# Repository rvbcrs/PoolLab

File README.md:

## Pura — ESP32‑S3 zwembadmonitor (pH, ORP, Temp · LVGL · MQTT · Zigbee)

### Wat het doet
- **pH en ORP meten** via analoge PH‑4502C/ORP‑4502C sensorbordjes (MCP6002 op 3.3 V) rechtstreeks op de ESP32 ADC.
- **Twee modi**: schakel tussen **Zigbee** en **WiFi/MQTT** via een UI‑toggle. De keuze wordt persistent opgeslagen (NVS) en bij boot toegepast.
- **MQTT integratie**: publiceert pH/ORP/temperatuur en biedt Home Assistant auto‑discovery + command topics om drempels te wijzigen.
- **Doseer‑pompen**: twee peristaltische pompen (pH/ORP) via TB6612FNG driver, met PWM‑snelheidsregeling vanuit de LVGL‑UI.
- **Safety**: limieten voor dagvolume, sessieduur en pH/ORP sanity; automatische noodstop + WhatsApp‑notificatie.
- **Zigbee commissioning**: lange druk op BOOT (>3 s) start commissioning; WiFi wordt tijdelijk uitgezet.

---

### Primaire hardware

| Onderdeel | Omschrijving |
|-----------|-------------|
| **MCU** | JC3248W535 — ESP32‑S3, 3.5" IPS 320×480 QSPI display, capacitief touch |
| **Sensoren** | 2× PH‑4502C bordje (één voor pH, één voor ORP), LM358 vervangen door **MCP6002** |
| **Motor driver** | SparkFun ROB‑14450 / TB6612FNG |
| **Pompen** | 2× peristaltische pomp (pH‑dosering en ORP/chloor‑dosering) |

---

### Sensor bekabeling (PH‑4502C met MCP6002 op 3.3 V)

> **Belangrijk:** Voed het bordje op **3.3 V**, niet 5 V.
> De MCP6002 is rail‑to‑rail (1.8–6 V). Bij 5 V kan de analoge output bij zuur water boven 3.3 V uitkomen en de ESP32 ADC beschadigen.

```
PH‑4502C (pH bordje)        JC3248W535 (ESP32‑S3)
  VCC  ──────────────────────  3.3 V
  GND  ──────────────────────  GND
  PO   ──────────────────────  GPIO6   (ADC1_CH5)
  DO   niet aansluiten
  TO   niet aansluiten
  BNC  ←── pH‑electrode

PH‑4502C (ORP bordje)       JC3248W535 (ESP32‑S3)
  VCC  ──────────────────────  3.3 V
  GND  ──────────────────────  GND
  PO   ──────────────────────  GPIO7   (ADC1_CH6)
  DO   niet aansluiten
  TO   niet aansluiten
  BNC  ←── ORP‑electrode
```

GPIO6 en GPIO7 zijn vrije ADC1‑pinnen (geen WiFi‑conflict). De overige ADC1‑pinnen zijn in gebruik door QSPI‑display (21/39/40/45/47/48), touch I2C (4/8), motoren (9/14–18) en I2S‑speaker (2/41/42).

**Testen zonder probe:**
Verbind de BNC center pin met de BNC outer ring via een 10 kΩ weerstand → simuleert 0 mV (pH 7 / 0 mV ORP) → de display toont ~pH 7.0 en ~0 mV.

**Platformio.ini flags (al ingesteld voor `esp32‑s3‑35`):**
```ini
-D USE_ANALOG_SENSORS=1
-D PH_ADC_PIN=6
-D ORP_ADC_PIN=7
```

**Kalibratie defaults (MCP6002 op 3.3 V, gain ≈ 5.2×):**
| Punt | Spanning |
|------|---------|
| pH 4 | ≈ 2.58 V |
| pH 7 | ≈ 1.65 V (mid‑supply) |
| pH 10 | ≈ 0.72 V |
| ORP 0 mV | ≈ 1.65 V |

Kalibreer altijd met pH 4 en pH 7 buffervloeistof voor nauwkeurige metingen. Waarden worden opgeslagen in NVS via WebUI → Settings → Calibration.

---

### Wiring diagrams

**ESP32‑S3 — Analoge sensoren (PH‑4502C met MCP6002)**

```mermaid
flowchart LR
  PH_PROBE["pH‑electrode\n(BNC)"] --> PH_BOARD["PH‑4502C\n(MCP6002 op 3.3 V)"]
  ORP_PROBE["ORP‑electrode\n(BNC)"] --> ORP_BOARD["PH‑4502C ORP\n(MCP6002 op 3.3 V)"]
  PH_BOARD  --"PO → GPIO6"--> MCU["JC3248W535\nESP32‑S3"]
  ORP_BOARD --"PO → GPIO7"--> MCU
  V33["3.3 V"] --> PH_BOARD
  V33         --> ORP_BOARD
  GND["GND"]  --> PH_BOARD
  GND         --> ORP_BOARD
  GND         --> MCU
```

**ESP32‑C6 — ADS1115 via I2C**

```mermaid
flowchart LR
  PH_PROBE["pH‑electrode\n(BNC)"] --> PH_BOARD["PH‑4502C"]
  ORP_PROBE["ORP‑electrode\n(BNC)"] --> ORP_BOARD["PH‑4502C ORP"]
  PH_BOARD  --"AO → A0"--> ADS["ADS1115\n(0x48)"]
  ORP_BOARD --"AO → A1"--> ADS
  ADS --"SDA → GPIO18"--> MCU["ESP32‑C6"]
  ADS --"SCL → GPIO19"--> MCU
  V33["3.3 V"] --> ADS
  GND["GND"]   --> ADS
  GND          --> MCU
```

**ESP32‑S3 — Motor driver (TB6612FNG)**

```mermaid
flowchart LR
  MCU["JC3248W535\nESP32‑S3"] --"GPIO15 IN1\nGPIO16 IN2\nGPIO17 PWM"--> M1["TB6612\nMotor A"]
  MCU --"GPIO18 IN1\nGPIO14 IN2\nGPIO9 PWM"--> M2["TB6612\nMotor B"]
  MCU --"GPIO46 STBY"--> M1
  MCU --"GPIO46 STBY"--> M2
  M1 --"A01/A02"--> PUMP1["pH‑pomp"]
  M2 --"B01/B02"--> PUMP2["ORP‑pomp"]
  VM["6–12 V"] --> M1
  VM           --> M2
```

---

### ADS1115 (ESP32‑C6 build)

De C6‑build (`esp32‑c6‑147`) leest pH en ORP via een ADS1115 16‑bit ADC op I2C:

```
ADS1115          ESP32‑C6
  VDD ────────── 3.3 V
  GND ────────── GND
  SDA ────────── GPIO18
  SCL ────────── GPIO19
  A0  ────────── pH AO
  A1  ────────── ORP AO
```

Flags (al ingesteld):
```ini
-D USE_ADS1115=1
-D ADS_ADDR=0x48
-D ADS_SDA=18
-D ADS_SCL=19
-D ADS_CH_PH=0
-D ADS_CH_ORP=1
```

---

### Motor driver bekabeling (TB6612FNG — ESP32‑S3)

```
TB6612FNG        JC3248W535 (ESP32‑S3)
  VCC  ────────── 3.3 V  (logica)
  GND  ────────── GND
  VM   ────────── motorspanning (6–12 V)
  STBY ────────── GPIO46

  AIN1 ────────── GPIO15  (M1 IN1 / pH pomp)
  AIN2 ────────── GPIO16  (M1 IN2)
  PWMA ────────── GPIO17  (M1 PWM — LEDC CH5 / Timer 3)

  BIN1 ────────── GPIO18  (M2 IN1 / ORP pomp)
  BIN2 ────────── GPIO14  (M2 IN2)
  PWMB ────────── GPIO9   (M2 PWM — LEDC CH4 / Timer 2)

  A01/A02 ─────── Motor 1 (pH‑pomp)
  B01/B02 ─────── Motor 2 (ORP‑pomp)
```

- GPIO46 is een strapping pin; zorg dat STBY niet omlaag trekt tijdens boot.
- PWM: 10 kHz, 8‑bit. Snelheden instelbaar in LVGL‑UI en opgeslagen in NVS.

---

### Pump Flow Tracking & Kalibratie

**Wat wordt bijgehouden:**
- Real‑time flow rate (ml/min) tijdens pompen
- Session volume (ml) — reset bij stop
- Daily volume — reset automatisch om 00:00
- Total volume — handmatig reset via WebUI

**Flow kalibreren:**
1. WebUI → Settings → "Pump Flow Rate (ml/min @ 100%)"
2. Laat pomp 60 s @ 100% draaien, meet volume in maatbeker
3. Flow rate = gemeten volume / 1 minuut
4. Systeem schaalt automatisch voor lagere snelheden (bijv. 60% = 0.6 × gekalibreerde waarde)

---

### Safety Features & Emergency Stop

**Limieten (instelbaar in `src/main.cpp`):**
```cpp
MAX_DAILY_VOLUME     = 500.0f;  // ml/dag per pomp
MAX_SESSION_VOLUME   = 200.0f;  // ml per aanslag
MAX_SESSION_DURATION = 120;     // seconden per aanslag
PH_SANITY_MIN        = 4.0f;
PH_SANITY_MAX        = 10.0f;
ORP_SANITY_MIN       = -500.0f;
ORP_SANITY_MAX       = 1500.0f;
SENSOR_TIMEOUT       = 300;     // seconden zonder data → alarm
```

**Gedrag bij trigger:**
- Alle pompen direct gestopt
- Rode banner op LVGL UI: `⚠️ EMERGENCY STOP - <reden>`
- MQTT alert op `pool/alert/<type>`
- WhatsApp‑bericht via CallMeBot

**WhatsApp Setup (CallMeBot):**
1. Verkrijg API key via https://www.callmebot.com/blog/free-api-whatsapp-messages/
2. WebUI → Safety → telefoonnummer (bijv. `31612345678`) + API key invullen
3. Test via "Send Test Alert" button

**MQTT Alert Topics:**
```
pool/alert/daily_limit_m1      pool/alert/daily_limit_m2
pool/alert/session_volume_m1   pool/alert/session_volume_m2
pool/alert/session_duration_m1 pool/alert/session_duration_m2
pool/alert/ph_sanity_low       pool/alert/ph_sanity_high
pool/alert/orp_sanity_low      pool/alert/orp_sanity_high
pool/alert/ph_sensor_timeout   pool/alert/orp_sensor_timeout
```

---

### Bouwen en flashen

Primaire build (ESP32‑S3 35"):
```bash
pio run -e esp32-s3-35 -t upload --upload-port <ip>   # OTA
pio run -e esp32-s3-35 -t upload                       # USB
```

C6 build:
```bash
pio run -e esp32-c6-147 -t upload
```

Seriële monitor: 115200 baud.

---

### Configuratie

**WiFi** via captive portal:
- Bij lege WiFi‑gegevens start automatisch AP `Pura‑Setup`.
- Verbind → open willekeurige URL → vul SSID/wachtwoord in → Save & Reboot.
- Of via Settings → Network → Configure WiFi.

**MQTT** instelbaar via WebUI → Settings (host/port/user/pass) of in `src/main.cpp`:
```cpp
MQTT_HOST, MQTT_PORT, MQTT_USER, MQTT_PASS, MQTT_CLIENTID
```

**OTA:** hostnaam `pura-XXXXXX` (chip‑ID). Upload via PlatformIO "Upload using network" of ArduinoOTA.

---

### MQTT Topics

State:
```
pool/sensor/ph
pool/sensor/orp
pool/sensor/temp
```

Home Assistant discovery:
```
homeassistant/sensor/pool_ph/config
homeassistant/sensor/pool_orp/config
homeassistant/sensor/pool_temp/config
```

Drempels (write/echo):
```
pool/cmd/ph_min  ↔  pool/cfg/ph_min
pool/cmd/ph_max  ↔  pool/cfg/ph_max
pool/cmd/orp_min ↔  pool/cfg/orp_min
pool/cmd/orp_max ↔  pool/cfg/orp_max
```

---

### WebUI

| URL | Pagina |
|-----|--------|
| `http://<ip>/` | Live sensor tiles + pump stats (WebSocket) |
| `http://<ip>/settings` | pH/ORP drempels, pompsnelheden, flow kalibratie, MQTT |
| `http://<ip>/safety` | Emergency status, WhatsApp config, volume resets, test alerts |

WebSocket op poort 81.

---

### LVGL UI

- **ESP32‑S3 (3.5"):** 3‑card UI (pH / ORP / Temp), moderne donkere tegels, pump stats boven motoricoon, emergency banner.
- **ESP32‑C6 (1.47"):** Compacte tileview (pH/ORP).
- Watchdog S3: heartbeat uit BSP‑task; herbouwt UI als >8 s stil → `S3 LVGL watchdog: rebuild complete`.
- Touch: debouncing ingebouwd, geen key‑repeat.

---

### Projectstructuur

| Bestand | Rol |
|---------|-----|
| `src/main.cpp` | Bootvolgorde, WiFi/MQTT, Zigbee, periodic publish, safety |
| `src/core/Storage.{h,cpp}` | NVS wrapper (drempels, snelheden, modus, volumes, config) |
| `src/core/boards/Esp32S3Board.{h,cpp}` | S3 board: display, touch, pins, LVGL lock |
| `src/core/boards/Esp32C6Board.{h,cpp}` | C6 board |
| `src/boards/BoardSelect.{h,cpp}` | Board‑selectie op basis van build flag |
| `src/domain/Metrics.{h,cpp}` | Laatste pH/ORP/temp; bron voor UI en MQTT |
| `src/domain/ControlPolicy.{h,cpp}` | Safety logic, sanity checks, emergency stop |
| `src/io/AnalogPhOrpSensor.h` | ADC‑lezer voor PH‑4502C via ESP32 ADC (S3) |
| `src/io/AdsPhOrpSensor.{h,cpp}` | ADS1115 I2C lezer voor pH/ORP (C6) |
| `src/io/MotorController.h` | Motor state machine, LEDC PWM, flow tracking |
| `src/io/MqttClient.{h,cpp}` | PubSubClient: discovery, publish, command topics, alerts |
| `src/io/WebUI.{h,cpp}` | Async web server: homepage, settings, safety, WebSocket, API |
| `src/io/ZigbeeClient.{h,cpp}` | Zigbee abstractie (C6; no‑op op S3) |
| `src/ui/UI.{h,cpp}` | LVGL UI builder (3‑card S3 / tileview C6), emergency banner |
| `src/domain/DummySensor.h` | Gesimuleerde sensordata voor testen |
| `src/fonts`, `src/images` | LVGL assets (fonts, iconen) |

---

### Troubleshooting

**pH/ORP waarden kloppen niet:**
- Kalibreer met pH 4 en pH 7 buffervloeistof via WebUI → Settings → Calibration.
- Check de spanning op PO met een multimeter: bij VCC=3.3 V moet pH 7 ≈ 1.65 V geven.
- Zorg dat VCC van het sensorbordje echt 3.3 V is (niet 5 V).

**WiFi "NO_AP_FOUND":** controleer SSID/ontvangst; auto‑reconnect + periodieke hard restart.

**MQTT extern werkt niet, lokaal wel:**
- Cloudflare DNS: zet op "DNS only" (grijze wolk) voor raw TCP.
- NPM: gebruik Streams (TCP), geen Proxy Host.
- Test met `mosquitto_sub/pub` voordat je het device test.

**Pompen werken niet:**
- Console: `[MOTOR] Check: MOTOR_ENABLE=1 motorsEnabled=?` — beide moeten 1 zijn.
- WebUI → Settings → vink "Enable pH/ORP dosing pumps" aan → Save.

**Emergency stop reset niet automatisch:**
- Sanity alerts: wacht tot sensorwaarden terug binnen limieten zijn.
- Volume/duration limits: reset device of wacht tot 00:00 (daily reset).

**WhatsApp notificaties werken niet:**
- Telefoonnummer met landcode (bijv. `31612345678`).
- Test via CallMeBot website om te bevestigen dat account actief is.
- Console: zoek naar `[SAFETY] WhatsApp API response: 200`.

---

### Changelog

**Huidig:**
- ✅ Tuya UART sniffer verwijderd — alle sensordata nu via directe hardware (ADC / ADS1115).
- ✅ PH‑4502C analoge sensoren op GPIO6 (pH) en GPIO7 (ORP) — MCP6002 op 3.3 V.
- ✅ Kalibratie defaults aangepast voor MCP6002 op 3.3 V (mid‑supply = 1.65 V).
- ✅ Zigbee `onPh/OrpMinMaxWrite` stubs voor non‑Zigbee builds (fix compile‑fout S3).
- ✅ `core::Board.h` include toegevoegd aan `UI.cpp` (fix `UiConfig` compile‑fout).
- ✅ Backup‑bestanden opgeruimd (`AnalogPhOrpSensor 2.h`, `AdsPhOrpSensor 2.*`).

**Eerder:**
- ✅ Pump flow tracking: ml/min, session, daily (auto‑reset 00:00), total.
- ✅ Safety limits: daily/session volume, session duration, pH/ORP sanity, sensor timeout.
- ✅ Emergency stop: noodstop + rode LVGL banner.
- ✅ WhatsApp notificaties via CallMeBot (async task).
- ✅ MQTT alert topics `pool/alert/<type>`.
- ✅ WebUI Safety page, Settings gereorganiseerd met emoji‑headers.
- ✅ Unieke MQTT clientId per device (chip‑ID).
- ✅ Exponential backoff bij MQTT reconnect.
- ✅ LVGL watchdog voor C6 en S3.
- ✅ Touch debouncing (geen key‑repeat).
- ✅ Reset WiFi knop via captive portal.

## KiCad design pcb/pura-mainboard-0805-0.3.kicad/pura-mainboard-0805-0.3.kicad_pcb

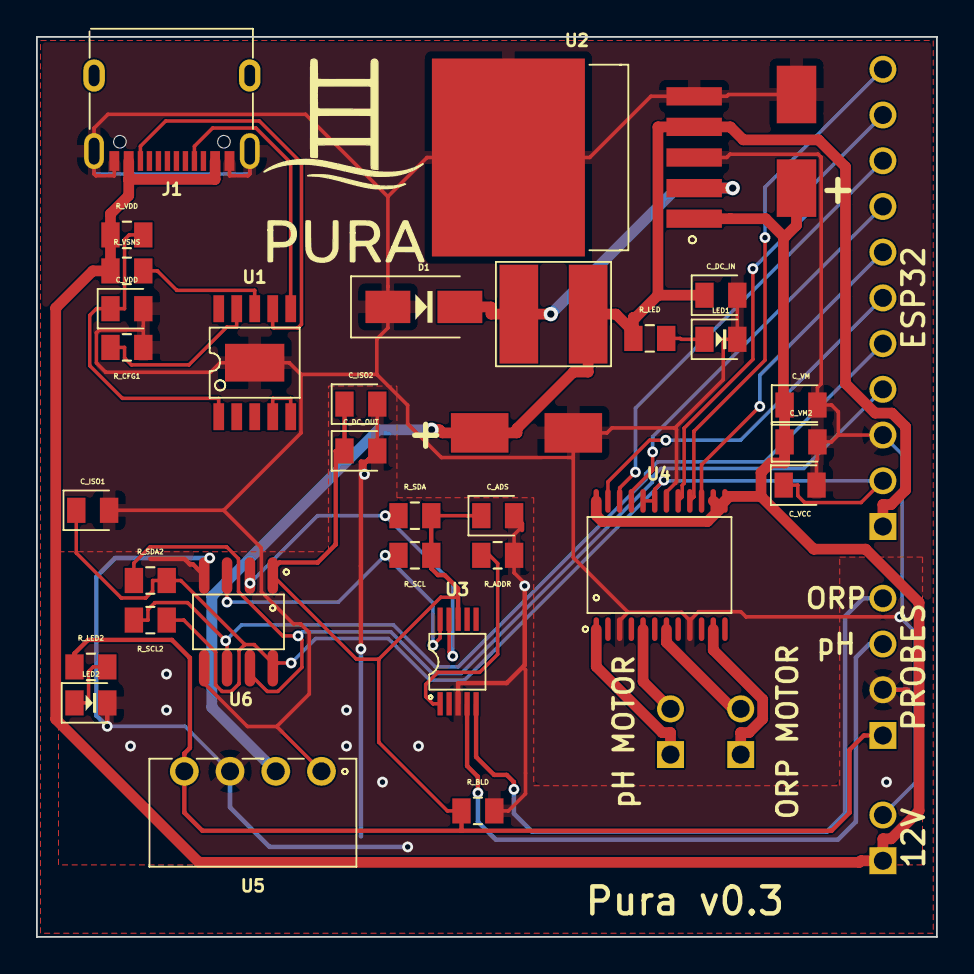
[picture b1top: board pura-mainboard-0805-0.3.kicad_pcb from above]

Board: 2 copper layers, 50.0 x 50.0 mm, 38 parts (0 on the bottom side), 32 nets.

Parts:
C_ADS: 100nF; capacitor_0805
C_DC_IN: 10uF; capacitor_0805
C_DC_OUT: 10uF; capacitor_0805
C_IN: 100uF; capacitor
C_ISO1, C_ISO2: 100nF; capacitor_0805
C_OUT: 220uF; capacitor
C_VCC: 100nF; capacitor_0805
C_VDD: 1uF; capacitor_0805
C_VM: 10uF; capacitor_0805
C_VM2: 100nF; capacitor_0805
D1: D; SS34
J1: TYPE_C_16PIN_2MD_073_; TYPE_C_16PIN_2MD_073
J_12V: J_12V; pin_header_pinrow2_nopinlabels
J_ESP: J_ESP; pin_header_pinrow11_nopinlabels
J_M1: J_M1; pin_header_pinrow2_nopinlabels
J_M2: J_M2; pin_header_pinrow2_nopinlabels
J_PROBE: J_PROBE; pin_header_pinrow4_nopinlabels
L1: 33H; inductor
LED1: LED; led_0805_color(green)
LED2: LED; led_0805_color(cyan)
R_ADDR: 0Ω; resistor_res0805
R_BLD: 330Ω; resistor_res0805
R_CFG1: 24kΩ; resistor_res0805
R_LED, R_LED2: 2.2kΩ; resistor_res0805
R_SCL, R_SCL2: 4.7kΩ; resistor_res0805
R_SDA, R_SDA2: 4.7kΩ; resistor_res0805
R_VDD: 1kΩ; resistor_res0805
R_VSNS: 10kΩ; resistor_res0805
U1: CH224K
U2: LM2596S_5_0_UMW_; LM2596S_5_0_UMW
U3: ADS1115IDGST
U4: TB6612FNG_C_8_EL
U5: B0505S_1WR3
U6: ADUM1250ARZ_RL7

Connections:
.J1 > .A4B9 to .R_VDD > .pin1: C_IN.1, C_VM.1, C_VM2.1, J1.18, J1.27, J_12V.1, R_VDD.1, R_VSNS.1, U2.1, U4.13, U4.14, U4.24
.J1 > .A5 to .U1 > .CC2: J1.20, U1.6
.J1 > .B5 to .U1 > .CC1: J1.26, U1.7
.J_ESP > .SCL to .U6 > .SCL2: J_ESP.5, R_SCL2.1, U6.6
.J_ESP > .SDA to .U6 > .SDA2: J_ESP.4, R_SDA2.1, U6.7
.J_ESP > .V33 to .U4 > .VCC: C_ISO1.1, C_VCC.1, J_ESP.2, R_SCL2.2, R_SDA2.2, U4.19, U4.20, U6.8
.L1 > .pin2 to .U2 > .FB: C_DC_IN.1, C_OUT.1, J_ESP.1, L1.2, R_LED.1, U2.4, U5.2
.R_LED2 > .pin2 to .LED2 > .pin1: LED2.1, R_LED2.2
.R_LED > .pin2 to .LED1 > .pin1: LED1.1, R_LED.2
.R_VDD > .pin2 to .U1 > .VDD: C_VDD.1, R_VDD.2, U1.1
.R_VSNS > .pin2 to .U1 > .VBUS: R_VSNS.2, U1.8
.U1 > .CFG1 to .R_CFG1 > .pin1: R_CFG1.1, U1.9
.U1 > .DP to .U1 > .DM: U1.4, U1.5
.U2 > .OUT to .L1 > .pin1: D1.2, L1.1, U2.2
.U3 > .ADDR to .R_ADDR > .pin1: R_ADDR.1, U3.1
.U3 > .AIN0 to .J_PROBE > .PH_PO: J_PROBE.3, U3.4
.U3 > .AIN1 to .J_PROBE > .ORP_PO: J_PROBE.4, U3.5
.U3 > .SCL to .R_SCL > .pin1: R_SCL.1, U3.10, U6.3
.U3 > .SDA to .R_SDA > .pin1: R_SDA.1, U3.9, U6.2
.U4 > .AIN1 to .J_ESP > .AIN1: J_ESP.8, U4.21
.U4 > .AIN2 to .J_ESP > .AIN2: J_ESP.9, U4.22
.U4 > .AO11 to .J_M1 > .MA1: J_M1.1, U4.1
.U4 > .AO21 to .J_M1 > .MA2: J_M1.2, U4.5
.U4 > .BIN1 to .J_ESP > .BIN1: J_ESP.10, U4.17
.U4 > .BIN2 to .J_ESP > .BIN2: J_ESP.11, U4.16
.U4 > .BO11 to .J_M2 > .MB1: J_M2.1, U4.11
.U4 > .BO21 to .J_M2 > .MB2: J_M2.2, U4.7
.U4 > .PWMA to .J_ESP > .PWMA: J_ESP.6, U4.23
.U4 > .PWMB to .J_ESP > .PWMB: J_ESP.7, U4.15
.U5 > .pin4 to .U6 > .VDD1: C_ADS.1, C_DC_OUT.1, C_ISO2.1, J_PROBE.1, R_BLD.1, R_LED2.1, R_SCL.2, R_SDA.2, U3.8, U5.4, U6.1
AGND: C_ADS.2, C_DC_OUT.2, C_ISO2.2, J_PROBE.2, LED2.2, R_ADDR.2, R_BLD.2, U3.3, U5.3, U6.4
GND: C_DC_IN.2, C_IN.2, C_ISO1.2, C_OUT.2, C_VCC.2, C_VDD.2, C_VM.2, C_VM2.2, D1.1, J1.13, J1.14, J1.17, J1.28, J_12V.2, J_ESP.3, LED1.2, R_CFG1.2, U1.11, U2.3, U2.5, U2.6, U4.3, U4.9, U4.18, U5.1, U6.5

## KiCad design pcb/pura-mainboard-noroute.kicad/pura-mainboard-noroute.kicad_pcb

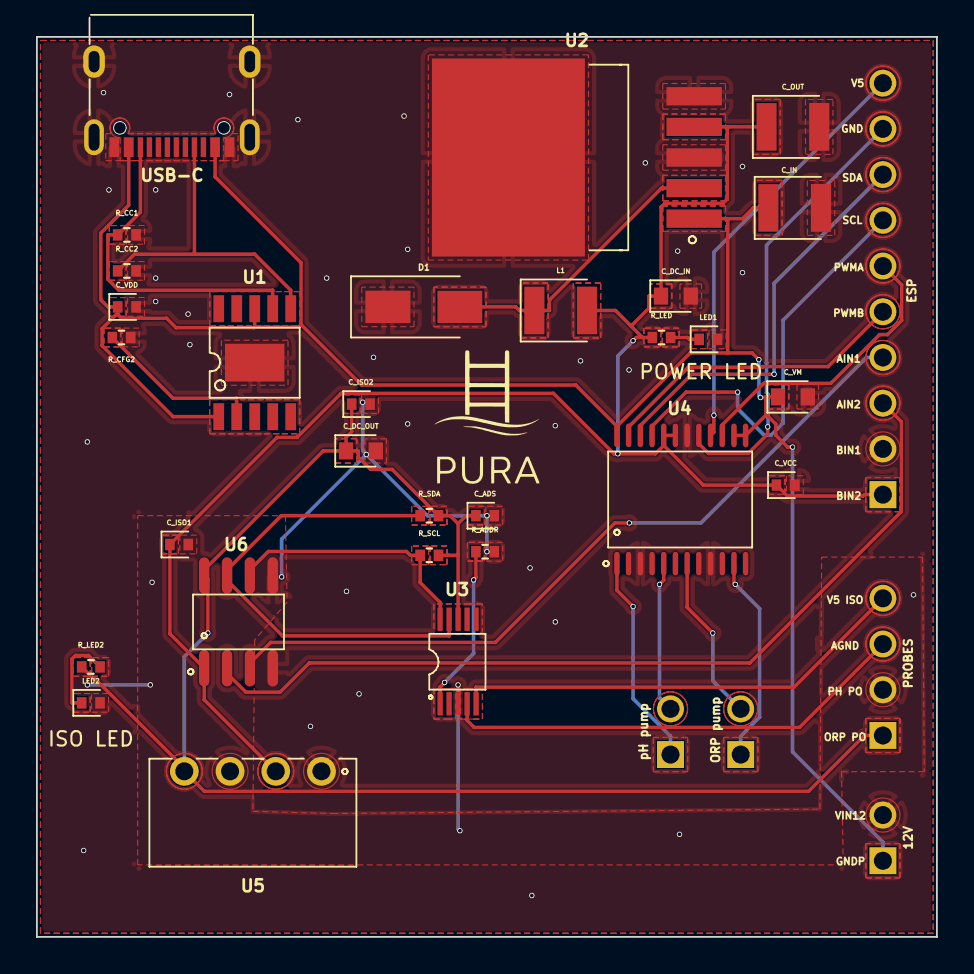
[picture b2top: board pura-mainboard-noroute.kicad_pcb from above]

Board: 2 copper layers, 50.0 x 50.0 mm, 34 parts (0 on the bottom side), 28 nets.

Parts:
12V: J_12V; pin_header_pinrow2_nopinlabels
C_ADS: 100nF; capacitor_0402
C_DC_IN: 10uF; capacitor_0603
C_DC_OUT: 10uF; capacitor_0603
C_IN: 220uF; capacitor_1210
C_ISO1, C_ISO2: 100nF; capacitor_0402
C_OUT: 220uF; capacitor_1210
C_VCC: 100nF; capacitor_0402
C_VDD: 100nF; capacitor_0402
C_VM: 10uF; capacitor_0603
D1: D; SS34
ESP: J_ESP; pin_header_pinrow10_nopinlabels
L1: 33H; inductor_1210
LED1: LED; led_0402_color(green)
LED2: LED; led_0402_color(cyan)
MOTOR 1: J_M1; pin_header_pinrow2_nopinlabels
ORP pump: J_M2; pin_header_pinrow2_nopinlabels
PROBES: J_PROBE; pin_header_pinrow4_nopinlabels
R_ADDR: 0Ω; resistor_res0402
R_CC1, R_CC2: 5.1kΩ; resistor_res0402
R_CFG2: 0Ω; resistor_res0402
R_LED, R_LED2: 2.2kΩ; resistor_res0402
R_SCL: 4.7kΩ; resistor_res0402
R_SDA: 4.7kΩ; resistor_res0402
U1: CH224K
U2: LM2596S_5_0_UMW_; LM2596S_5_0_UMW
U3: ADS1115IDGST
U4: TB6612FNG_C_8_EL
U5: B0505S_1WR3
U6: ADUM1250ARZ_RL7
USB-C: TYPE_C_16PIN_2MD_073_; TYPE_C_16PIN_2MD_073

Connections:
.J1 > .A5 to .U1 > .CC2: R_CC2.1, U1.6, USB-C.20
.J1 > .B5 to .U1 > .CC1: R_CC1.1, U1.7, USB-C.26
.J_ESP > .SCL to .U6 > .SCL1: ESP.4, U6.3
.J_ESP > .SDA to .U6 > .SDA1: ESP.3, U6.2
.L1 > .pin2 to .U2 > .FB: C_DC_IN.1, C_ISO1.1, C_OUT.1, C_VCC.1, ESP.1, L1.2, R_LED.1, U2.4, U4.19, U4.20, U5.2, U6.1
.R_LED2 > .pin2 to .LED2 > .pin1: LED2.1, R_LED2.2
.R_LED > .pin2 to .LED1 > .pin1: LED1.1, R_LED.2
.U1 > .CFG2 to .R_CFG2 > .pin1: R_CFG2.1, U1.2
.U1 > .VDD to .U1 > .VBUS: 12V.1, C_IN.1, C_VDD.1, C_VM.1, U1.1, U1.8, U2.1, U4.13, U4.14, U4.24, USB-C.18, USB-C.27
.U2 > .OUT to .L1 > .pin1: D1.2, L1.1, U2.2
.U3 > .ADDR to .R_ADDR > .pin1: R_ADDR.1, U3.1
.U3 > .AIN0 to .J_PROBE > .PH_PO: PROBES.3, U3.4
.U3 > .AIN1 to .J_PROBE > .ORP_PO: PROBES.4, U3.5
.U3 > .SCL to .R_SCL > .pin1: R_SCL.1, U3.10, U6.6
.U3 > .SDA to .R_SDA > .pin1: R_SDA.1, U3.9, U6.7
.U4 > .AIN1 to .J_ESP > .AIN1: ESP.7, U4.21
.U4 > .AIN2 to .J_ESP > .AIN2: ESP.8, U4.22
.U4 > .AO11 to .J_M1 > .MA1: MOTOR 1.1, U4.1
.U4 > .AO21 to .J_M1 > .MA2: MOTOR 1.2, U4.5
.U4 > .BIN1 to .J_ESP > .BIN1: ESP.9, U4.17
.U4 > .BIN2 to .J_ESP > .BIN2: ESP.10, U4.16
.U4 > .BO11 to .J_M2 > .MB1: ORP pump.1, U4.11
.U4 > .BO21 to .J_M2 > .MB2: ORP pump.2, U4.7
.U4 > .PWMA to .J_ESP > .PWMA: ESP.5, U4.23
.U4 > .PWMB to .J_ESP > .PWMB: ESP.6, U4.15
.U5 > .pin4 to .U6 > .VDD2: C_ADS.1, C_DC_OUT.1, C_ISO2.1, PROBES.1, R_LED2.1, R_SCL.2, R_SDA.2, U3.8, U5.4, U6.8
AGND: C_ADS.2, C_DC_OUT.2, C_ISO2.2, LED2.2, PROBES.2, R_ADDR.2, U3.3, U5.3, U6.5
GND: 12V.2, C_DC_IN.2, C_IN.2, C_ISO1.2, C_OUT.2, C_VCC.2, C_VDD.2, C_VM.2, D1.1, ESP.2, LED1.2, R_CC1.2, R_CC2.2, R_CFG2.2, U1.11, U2.3, U2.5, U2.6, U4.3, U4.9, U4.18, U5.1, U6.4, USB-C.13, USB-C.14, USB-C.15, USB-C.16, USB-C.17, USB-C.28

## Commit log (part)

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2025-09-10 Working version
2025-09-11 Refactor into logical structure
2025-09-12 First Zigbee implementation
2025-09-13 WIP zigbee sensors
2025-09-13 Working zigbee tx
2025-09-13 Touch fix
2025-09-13 Icons for zigbee connection
2025-09-13 Zigbee iJoined()
2025-09-13 Settings screen cleanup and zigbee bugfix
2025-09-14 Readme update and zigbee / wifi toggle fix
2025-09-15 Wifi Captha portal and OTA
2025-09-15 Unique ChipID for OTA and capcha
2025-09-15 Simple WebUI and readme update
2025-09-17 ESP32-S3-JC3248W535 board added
2025-09-19 Multiboard support and refactoring code from main
2025-09-22 UI fixes and further main cleanup
2025-09-22 More refactoring of main
2025-09-22 refactor main
2025-09-23 Settings bug fixes
2025-09-23 MQTT issues fix
2025-09-23 Removed debug logging mqtt
2025-09-24 MQTT fixes
2025-09-24 C6 Legacy ui deleted
2025-09-25 Temperature colored tile
2025-09-25 ADS1115 and ESP32 ADC sensor readings
2025-09-25 Readme mermaid fix
2025-10-02 Added flow and fixed touch
2025-10-04 Added fuel security and safety features
2025-10-06 Initial P4 board added
2025-10-09 Pump flow fix in ui
2025-10-09 Zigbee mode enabled for P4
2025-10-14 Fixes for P4
2025-10-21 Add ESP32-P4 display libraries (st7701_lcd + gt911_touch)
    - Added st7701_lcd library for MIPI-DSI LCD driver
    - Added gt911_touch library for capacitive touch driver
    - Libraries moved from lib_p4 to libraries folder
    - Working configuration with direct initialization in main.cpp
2025-10-25 Working display wrapper
2026-02-06 build: Generate PlatformIO build artifacts for ESP32P4 project, including LVGL, ESP32P4_Display, and GT911 touch libraries.
2026-02-06 feat: Add new STEP models for various components, STL files and a Python script for the case, and update `main.cpp`.
2026-02-07 refactor: Redesign case and lid components, introducing modular pump case parts and a new pump model.
2026-02-07 fix: refine mounting hole detection logic and adjust motor cutout diameter for pump case lid.
2026-02-07 feat: Add USB-C connector and update case designs for full assembly.
2026-02-07 fix: color changes
2026-02-07 feat: Update case and lid designs and regenerate the full assembly.
2026-02-07 feat: Add 'PoolLab' text as a flush inlay to the lid, refactor export logic, and include new font files.
2026-02-07 feat: Update CAD design files and generation script for the case and lid components.
2026-02-08 refactor: Redesign lid screen cutout and implement new recessed mounting brackets.
2026-02-08 feat: Adjust BNC Z-position and PCB Z-offset, reposition GX12, sensors, and other modules, restore USB-C clearance, and remove CTP09 wall cutout.
2026-02-08 feat: Adjust component positions and update geometry in CAD designs for case and lid.
2026-02-09 feat: Update CAD models with dimensional adjustments to the case and lid.
2026-02-09 feat: add power management with IP5306 and ADC support, update device CAD designs, and introduce an I2C scanner.
2026-02-10 feat: Implement web console and TelnetStream integration, alongside minor CAD design file updates.
2026-02-10 feat: Refine case pillar cutout and adjust internal component positions for GX12, sensors, and modules.
2026-02-17 feat: Add speaker support with UI control and resolve motor PWM timer conflicts for motor 1 and 2.
2026-02-18 feat: Enhance board support with unified Board class, implement board-specific configurations, and integrate CallMeBot API key management in storage.
2026-02-19 refactor: Remove unused Zigbee code and implement UI configuration structure for board-specific settings.
2026-02-19 feat: Replace Tuya sniffer with direct analog pH/ORP/Temp sensing, update platform to ESP32-S3, and clean up old files.
2026-02-19 feat: implement LVGL task heartbeat, refine dummy sensor mode, and remove obsolete pin configurations and test files.
2026-02-19 feat: Implement UI theme system with dark and light modes and persistent storage.
2026-02-19 Refactor UI scrolling and watchdog heartbeat logic, and update mechanical designs.
